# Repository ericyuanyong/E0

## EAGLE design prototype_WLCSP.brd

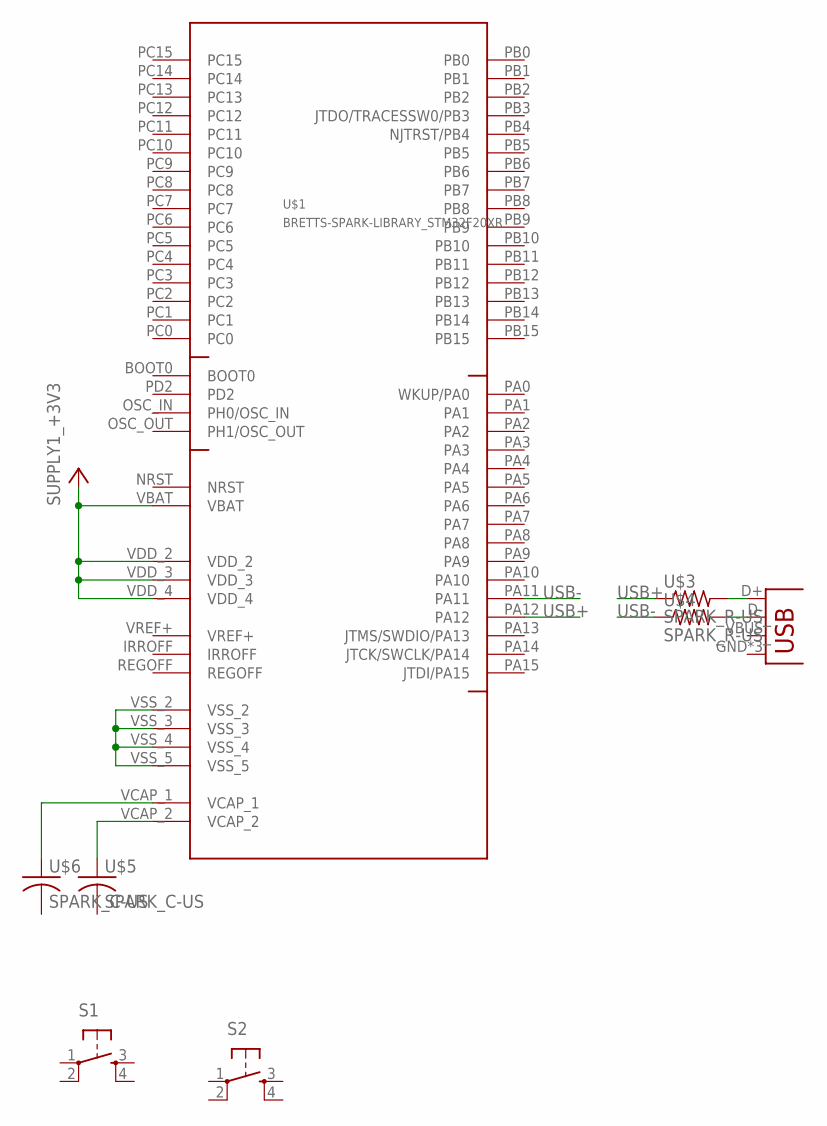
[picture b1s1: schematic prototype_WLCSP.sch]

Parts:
JP1: SPARK_USB-MICROB
S1, S2: SPARK_TAC_SWITCHSMD; SPARK_TACTILE_SWITCH_SMD
U$1: BRETTS-SPARK-LIBRARY_STM32F20XR; STM32F205_WLCSP
U$3, U$4: SPARK_R-US_; SPARK_R0402_B
U$5, U$6: SPARK_C-US; SPARK_C0402_B

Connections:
+3V3: U$1.VBAT, U$1.VDD_2, U$1.VDD_3, U$1.VDD_4
IRROFF: U$1.IRROFF
unnamed: JP1.D+, U$3.2
unnamed: JP1.D-, U$4.2
unnamed: U$1.VCAP_2, U$5.1
unnamed: U$1.VCAP_1, U$6.1
unnamed: U$1.VSS_2, U$1.VSS_3, U$1.VSS_4, U$1.VSS_5
NRST: U$1.NRST
USB+: U$1.PA12, U$3.1
USB-: U$1.PA11, U$4.1
VREF+: U$1.VREF+

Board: 2 copper layers, 8 parts (0 on the bottom side), 8 nets, no tracks yet.

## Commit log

2016-11-03 :neckbeard: Added .gitattributes & .gitignore files
2016-11-03 add a new folder for E0
2016-11-16 update the file
